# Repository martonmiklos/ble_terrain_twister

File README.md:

# ble_terrain_twister
nRF51822 based control board for the Hot Wheels Terrain Twister

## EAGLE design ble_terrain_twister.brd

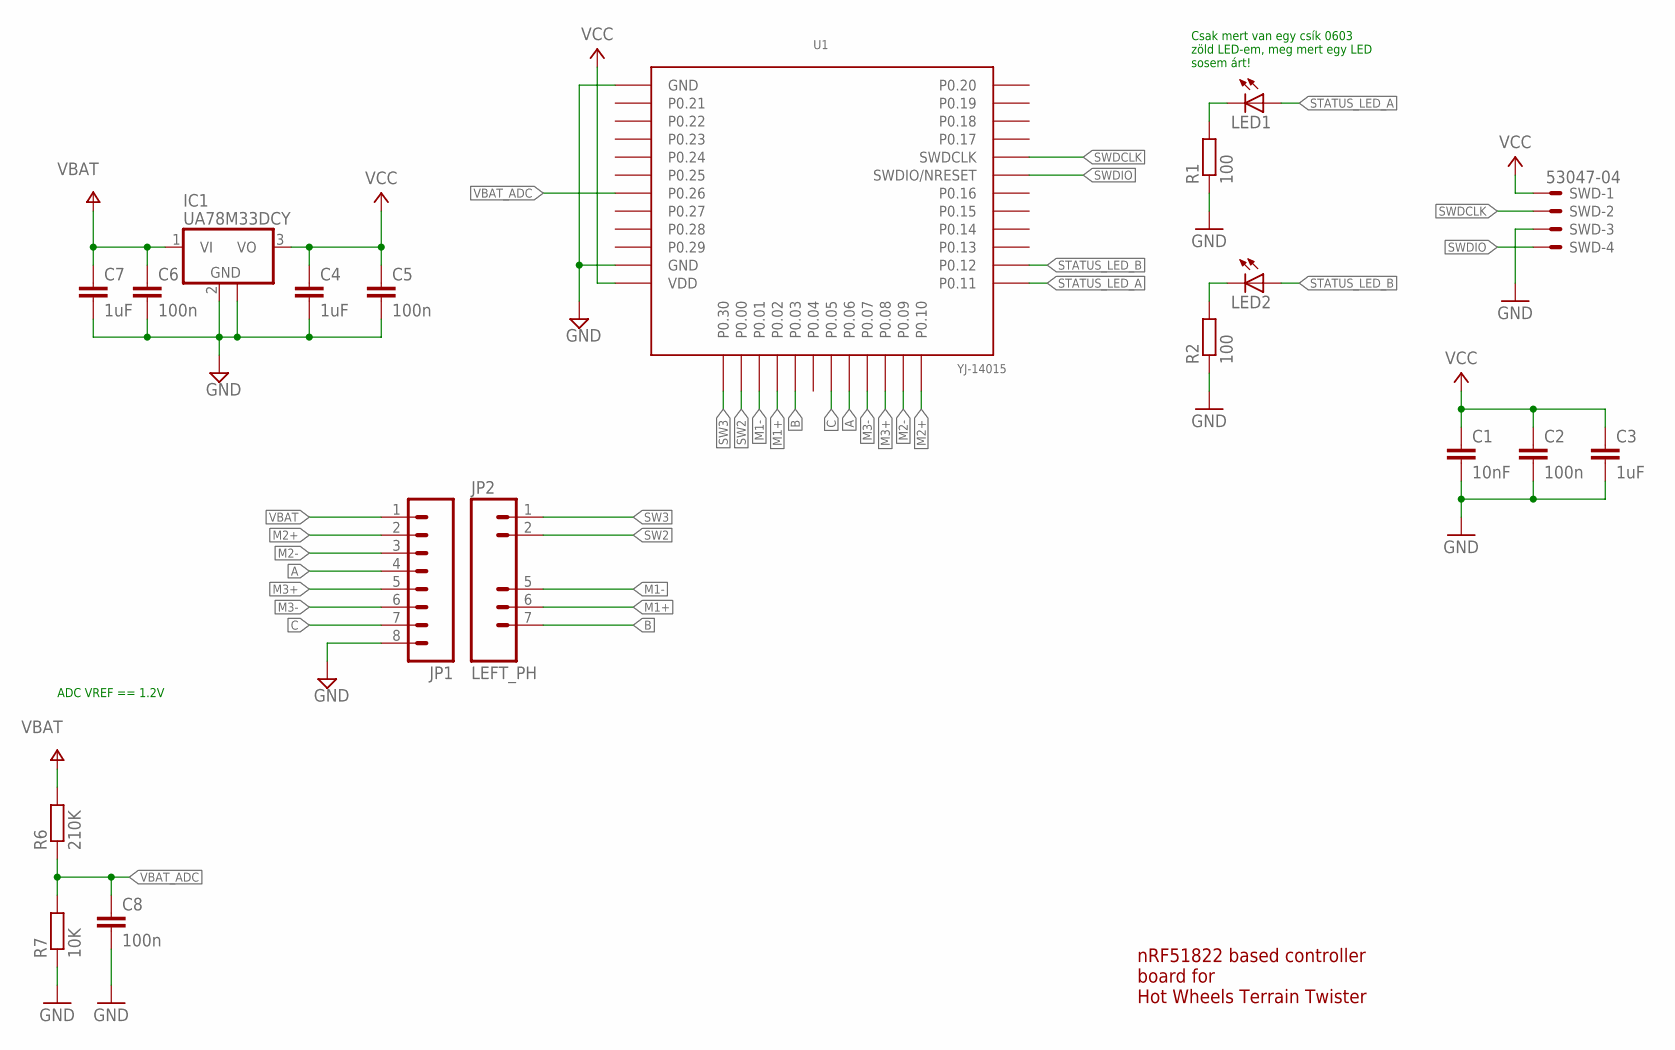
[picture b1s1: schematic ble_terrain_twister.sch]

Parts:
C1: 10nF; C0603
C2, C5, C6, C8: 100n; C0603
C3, C4, C7: 1uF; C0603
IC1: UA78M33DCY; SOT223
JP1: M081.27MM; 1X08_1.27MM
JP2: LEFT_PH; 1X08_1.27MM
LED1, LED2: LED0603; CHIPLED_0603
R1, R2: 100; R0603
R6: 210K; R0603
R7: 10K; R0603
SWD: 53047-04
U1: YJ-14015

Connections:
A: JP1.4, U1.P.06 (P0.06)
B: JP2.7, U1.P.03 (P0.03)
C: JP1.7, U1.P.05 (P0.05)
GND: C1.2, C2.2, C3.2, C4.2, C5.2, C6.2, C7.2, C8.2, IC1.2 (GND), IC1.4 (GND), JP1.8, R1.1, R2.1, R7.1, SWD.3, U1.GND, U1.GND@2 (GND)
LED_A_R: LED1.C, R1.2
LED_B_R: LED2.C, R2.2
M1+: JP2.6, U1.P.02 (P0.02)
M1-: JP2.5, U1.P.01 (P0.01)
M2+: JP1.2, U1.P.10 (P0.10)
M2-: JP1.3, U1.P.09 (P0.09)
M3+: JP1.5, U1.P.08 (P0.08)
M3-: JP1.6, U1.P.07 (P0.07)
STATUS_LED_A: LED1.A, U1.P.11 (P0.11)
STATUS_LED_B: LED2.A, U1.P.12 (P0.12)
SW2: JP2.2, U1.P.00 (P0.00)
SW3: JP2.1, U1.P.30 (P0.30)
SWDCLK: SWD.2, U1.SWDCLK
SWDIO: SWD.4, U1.SWDIO (SWDIO/NRESET)
VBAT: C6.1, C7.1, IC1.1 (VI), JP1.1, R6.2
VBAT_ADC: C8.1, R6.1, R7.2, U1.P.26 (P0.26)
VCC: C1.1, C2.1, C3.1, C4.1, C5.1, IC1.3 (VO), SWD.1, U1.VDD

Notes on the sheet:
nRF51822 based controller board for Hot Wheels Terrain Twister
ADC VREF == 1.2V
Csak mert van egy csík 0603 zöld LED-em, meg mert egy LED sosem árt!

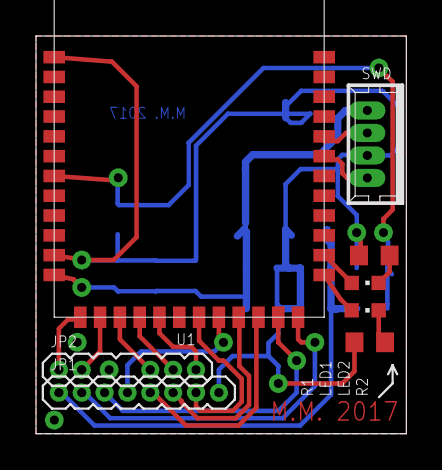
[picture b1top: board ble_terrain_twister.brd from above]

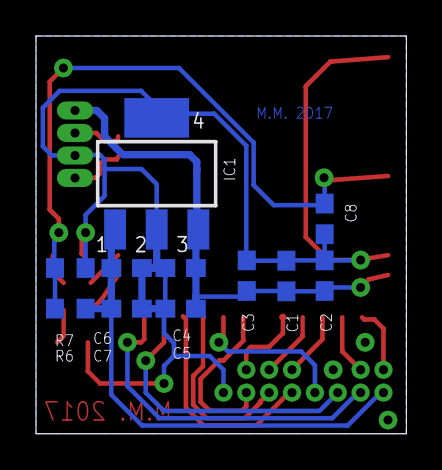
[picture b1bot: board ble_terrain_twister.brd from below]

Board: 2 copper layers, 20.6 x 22.1 mm, 19 parts (11 on the bottom side), 21 nets.

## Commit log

2017-09-14 Added CAD files
2017-09-18 Finished routing. again.
2017-09-19 Added PDF outputs.
2017-09-21 YJ-14015 footprint fixed
2017-10-12 Sikscreen cleanup before Gerberization

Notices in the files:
parts and their libraries:
SparkFun: Licensing: CC v3.0 Share-Alike You are welcome to use this library for commercial purposes.
